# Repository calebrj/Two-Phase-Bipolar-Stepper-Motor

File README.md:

# Two-Phase-Bipolar-Stepper-Motor
A repository of a PCB design made in KiCAD of a Two Phase Bipolar Stepper Motor. The repo contains a 3D view, the PCB schematic, the electrical schematic, gerber files and the bill of materials for manufacturer use.

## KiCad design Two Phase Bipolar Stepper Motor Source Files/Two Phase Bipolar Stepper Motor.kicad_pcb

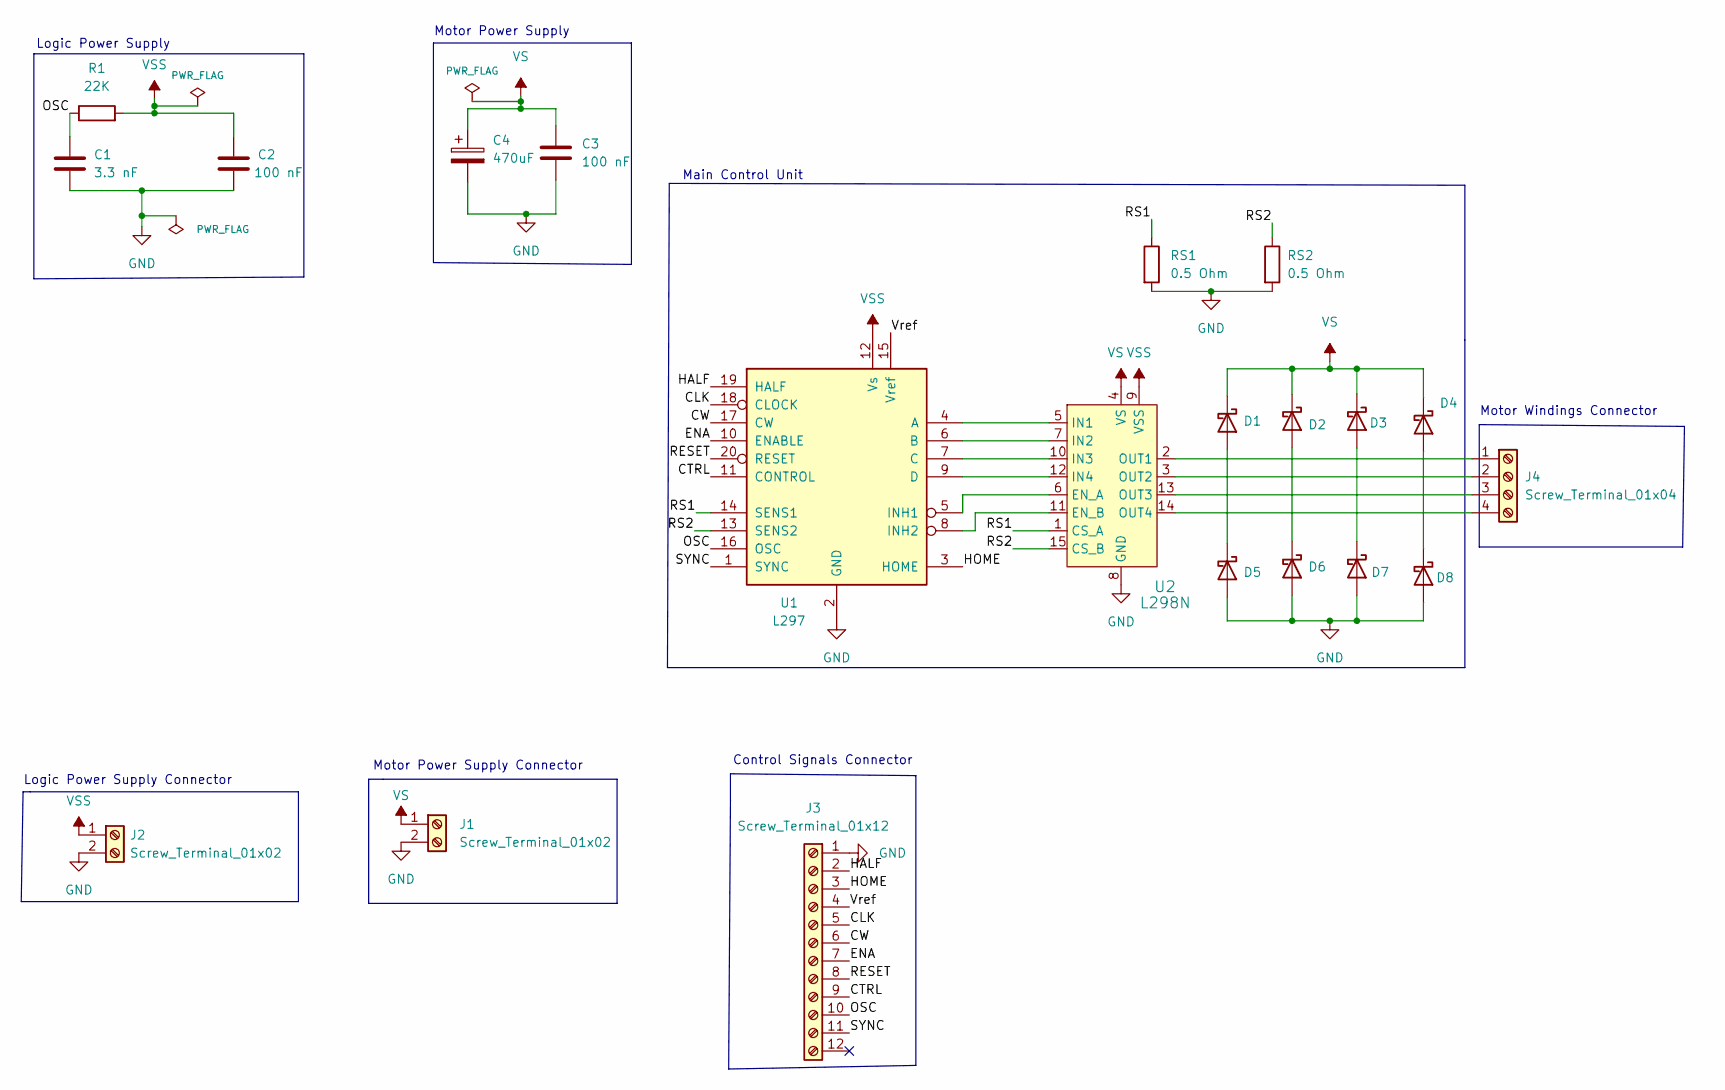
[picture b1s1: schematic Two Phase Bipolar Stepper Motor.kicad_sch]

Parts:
C1: 3.3 nF; C_Rect_L10.0mm_W4.0mm_P7.50mm_FKS3_FKP3
C2, C3: 100 nF; C_Rect_L7.5mm_W6.5mm_P5.00mm
C4: 470uF; CP_Radial_D13.0mm_P5.00mm
D1, D2, D3, D4, D5, D6, D7, D8: D_Schottky; D_DO-27_P15.24mm_Horizontal
J1, J2: Screw_Terminal_01x02; TerminalBlock_Phoenix_MKDS-1,5-2-5.08_1x02_P5.08mm_Horizont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
J3: Screw_Terminal_01x12; TerminalBlock_Phoenix_MKDS-1,5-12-5.08_1x12_P5.08mm_Horizon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
J4: Screw_Terminal_01x04; TerminalBlock_Phoenix_MKDS-1,5-4_1x04_P5.00mm_Horizontal
R1: 22K; R_Axial_DIN0922_L20.0mm_D9.0mm_P25.40mm_Horizontal
RS1, RS2: 0.5 Ohm; R_Axial_DIN0414_L11.9mm_D4.5mm_P15.24mm_Horizontal
U1: L297; DIP-20_W7.62mm
U2: L298N; TO127P2020X500X2100-15; MPN L298N; Digi-Key_PN 497-1395-5-ND

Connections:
/CLK: J3.5, U1.18 (CLOCK)
/CTRL: J3.9, U1.11 (CONTROL)
/CW: J3.6, U1.17 (CW)
/ENA: J3.7, U1.10 (ENABLE)
/HALF: J3.2, U1.19 (HALF)
/HOME: J3.3, U1.3 (HOME)
/OSC: C1.1, J3.10, R1.1, U1.16 (OSC)
/RESET: J3.8, U1.20 (RESET)
/RS1: RS1.1, U1.14 (SENS1), U2.1 (CS_A)
/RS2: RS2.1, U1.13 (SENS2), U2.15 (CS_B)
/SYNC: J3.11, U1.1 (SYNC)
/Vref: J3.4, U1.15 (Vref)
GND: C1.2, C2.2, C3.2, C4.2, D5.2 (A), D6.2 (A), D7.2 (A), D8.2 (A), J1.2, J2.2, J3.1, RS1.2, RS2.2, U1.2 (GND), U2.8 (GND)
unnamed: D3.2 (A), D7.1 (K)
unnamed: D4.2 (A), D8.1 (K)
unnamed: D1.2 (A), D5.1 (K)
unnamed: D2.2 (A), D6.1 (K)
unnamed: J4.1, U2.2 (OUT1)
unnamed: J4.2, U2.3 (OUT2)
unnamed: U1.4 (A), U2.5 (IN1)
unnamed: U1.5 (INH1), U2.6 (EN_A)
unnamed: U1.6 (B), U2.7 (IN2)
unnamed: U1.7 (C), U2.10 (IN3)
unnamed: U1.8 (INH2), U2.11 (EN_B)
unnamed: U1.9 (D), U2.12 (IN4)
unnamed: J4.3, U2.13 (OUT3)
unnamed: J4.4, U2.14 (OUT4)
VS: C3.1, C4.1, D1.1 (K), D2.1 (K), D3.1 (K), D4.1 (K), J1.1, U2.4 (VS)
VSS: C2.1, J2.1, R1.2, U1.12 (Vs), U2.9 (VSS)

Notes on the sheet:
Logic Power Supply Connector
Main Control Unit
Motor Power Supply Connector
Logic Power Supply
Motor Windings Connector
Motor Power Supply
Control Signals Connector

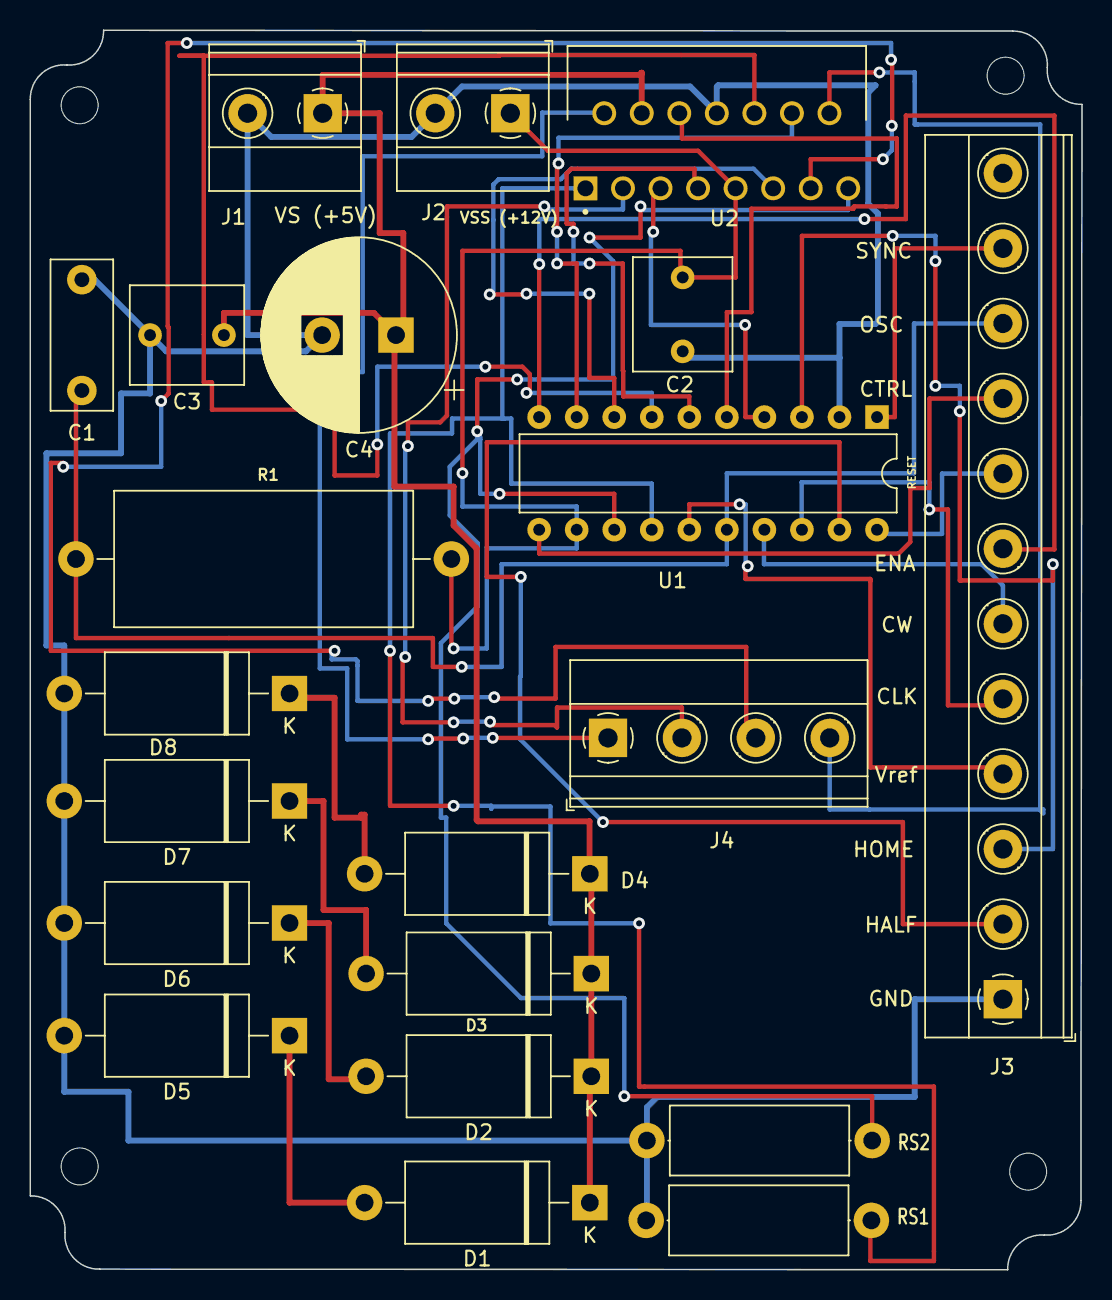
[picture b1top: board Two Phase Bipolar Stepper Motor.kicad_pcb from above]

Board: 2 copper layers, 71.2 x 83.9 mm, 21 parts (0 on the bottom side), 29 nets.

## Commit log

2022-07-15 Create Empty
